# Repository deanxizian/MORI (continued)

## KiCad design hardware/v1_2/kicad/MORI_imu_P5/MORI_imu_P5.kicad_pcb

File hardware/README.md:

# 硬件

当前成品为 **成品模块 + 一块自制驱动/载板**。原自制电源、IMU、后接口板已退出设计方向。

| 部分 | 当前选择/入口 |
|---|---|
| 自制驱动/载板 | [C3 R108P](driver/README.md)，40 项未连接，不可制造 |
| 主控 | WeAct STM32F412RET6 64Pin V1.1 |
| UPS | 微雪 UPS Module 3S，原配 DC 口与总开关 |
| IMU | DFRobot BMI323 / SEN0693，使用板载小插座 |
| 头部 | 微雪 CAM33700 / OV3660、1.85inch Touch LCD Module / LCD35079 |
| 舵机 | S288 ×2、SCS0009 SC-0090-C001 ×2 |
| 音频 | CAM 板载音频 + SP3040 喇叭 |

[采购记录](../mechanical/procurement/采购记录.md)记录已买状态和当时价格；[当前板 BOM](driver/bom_candidate.csv)是尚未发布制造的开发候选；[线束表](driver/harness/README.md)未给裁切长度。

正式共享合同仍为 [IF-C1-R4](../contracts/components.json)，C3 R108P 还未晋升合同。主模型是 M1.58，旧载板/外置 Buck 尚未替换。旧多板数据收在 [机械构建参考](../mechanical/input_assets/pcb_reference/README.md)，不是当前采购列表。

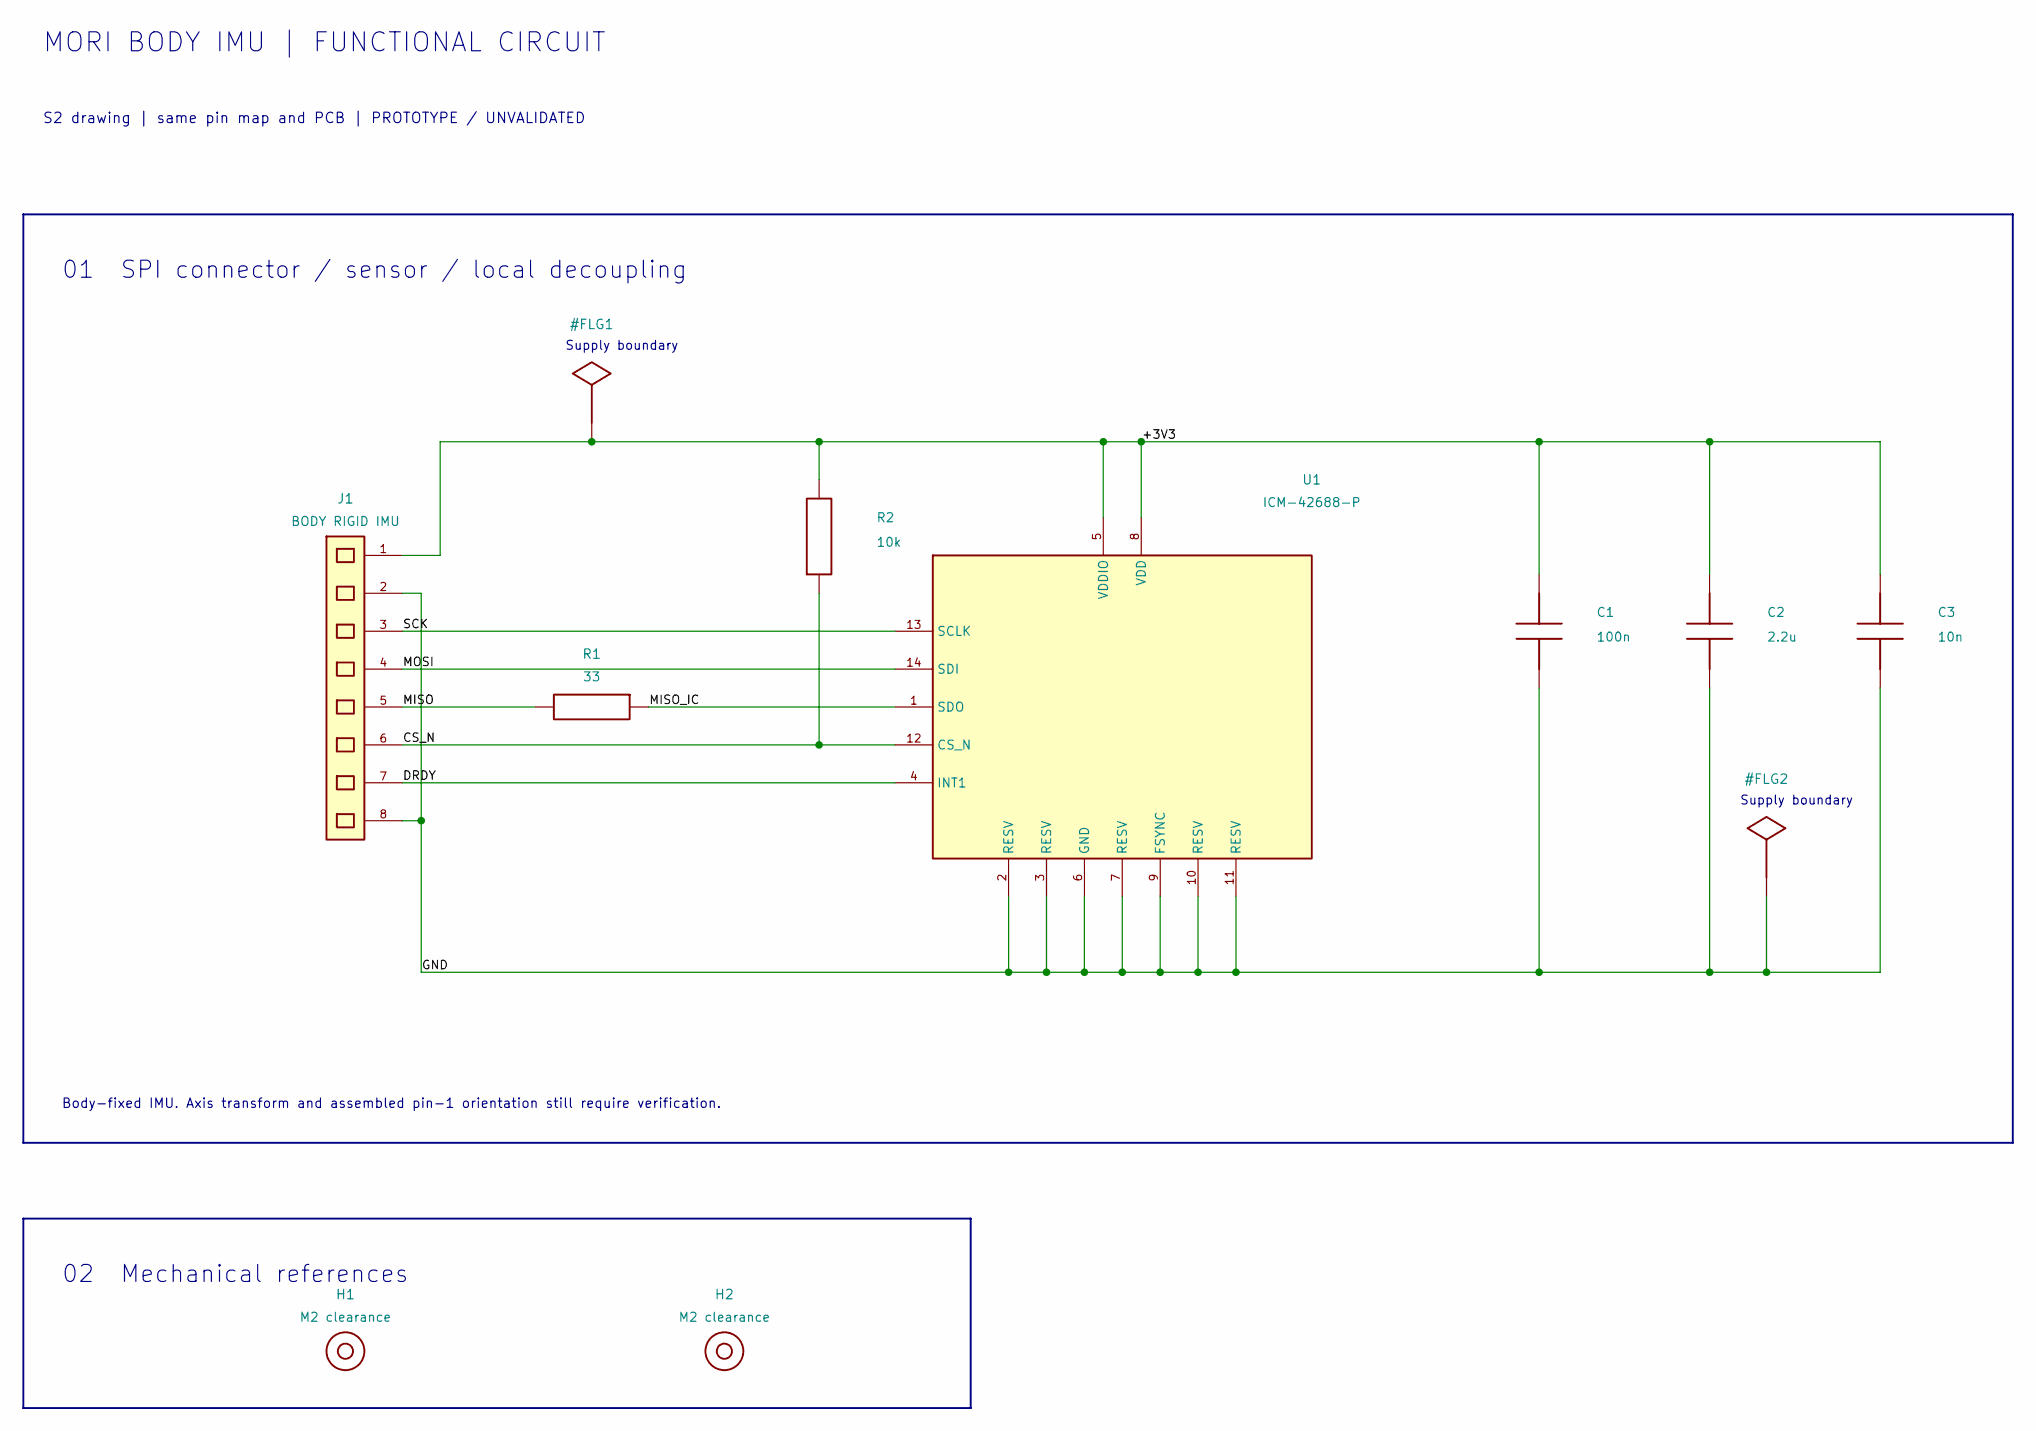
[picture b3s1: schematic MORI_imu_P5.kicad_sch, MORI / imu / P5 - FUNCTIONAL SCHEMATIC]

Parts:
C1: 100n; C_0603_1608Metric
C2: 2.2u; C_0603_1608Metric
C3: 10n; C_0603_1608Metric
H1, H2: M2 clearance; MountingHole_2.2mm_M2
J1: BODY RIGID IMU; JST_PH_B8B-PH-K_1x08_P2.00mm_Vertical__P4_PH_ANNULUS__P5_J1
R1: 33; R_0603_1608Metric
R2: 10k; R_0603_1608Metric
U1: ICM-42688-P; TDK_ICM42688P_LGA14_3x2p5__P2_U1__P3R1_U1

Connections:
/+3V3: C1.1, C2.1, C3.1, J1.1, R2.2, U1.5 (VDDIO), U1.8 (VDD)
/CS_N: J1.6, R2.1, U1.12 (CS_N)
/DRDY: J1.7, U1.4 (INT1)
/GND: C1.2, C2.2, C3.2, J1.2, J1.8, U1.2 (RESV), U1.3 (RESV), U1.6 (GND), U1.7 (RESV), U1.9 (FSYNC), U1.10 (RESV), U1.11 (RESV)
/MISO: J1.5, R1.2
/MISO_IC: R1.1, U1.1 (SDO)
/MOSI: J1.4, U1.14 (SDI)
/SCK: J1.3, U1.13 (SCLK)

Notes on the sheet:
MORI BODY IMU | FUNCTIONAL CIRCUIT
S2 drawing | same pin map and PCB | PROTOTYPE / UNVALIDATED
01 SPI connector / sensor / local decoupling
Body-fixed IMU. Axis transform and assembled pin-1 orientation still require verification.
Supply boundary
02 Mechanical references

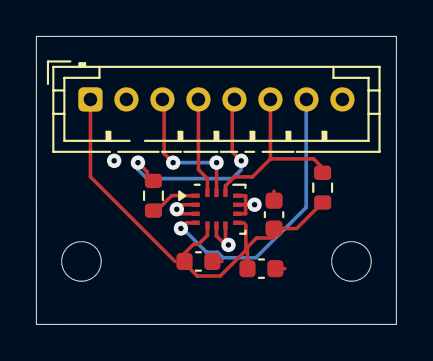
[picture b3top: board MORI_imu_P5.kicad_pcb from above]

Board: 2 copper layers, 20.0 x 16.0 mm, 9 parts (0 on the bottom side), 8 nets.

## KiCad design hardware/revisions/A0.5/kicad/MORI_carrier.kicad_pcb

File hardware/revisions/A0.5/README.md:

# MORI 硬件设计增量 A0.5

本轮已经完成保护电路补充、可复核的载板布线、固件修复和独立机械校核。**这是待实物验证的工程增量，尚未放行整机装配或PCB生产。** 原机械工程和A0.4档案保留；并行软件目录未改写。

## 已落地的内容

|内容|本轮结果|
|---|---|
|最小固件|修复ESP-IDF5.5.2的LEDC初始化遗漏；输出失败锁存并撤销ARM；实际构建通过；195项模拟断言通过|
|舵机信号|增加SN74LVC1T45的断电隔离、电源去耦和输出下拉；GPIO41与脉宽定义不变|
|原生KiCad|80个封装、1074条走线/过孔、2个GND铜区；ERC=0；DRC违规=0、未连接=0、原理图一致性问题=0|
|跨文件核对|242个引脚网络、94行载板接线；GPIO、默认运动锁定和原机械源保持一致|
|独立机械模型|主控与头部支柱的包络冲突已量化；电池托架加长；IMU真实孔位已加入|
|试打文件|电池托架54×92×7.45和IMU孔距试片30×22×2.4；闭合单实体，已重新导入校核尺寸|
|软件交接|Pololu4863 / 979.616计数每转继续作为硬件执行基线；无需等待电池与外壳定型才开始模拟/协议开发|

先看 [机械校核与试打件](mechanical/README.md)、[电路增量和布局限制](electrical_changes.md)、[软件接口决策](interface_decisions.md)、[验证记录](reports/verification.md)。采购仍按 [本版BOM](bom.csv) 的状态执行，未下单、未刷写、未生成Gerber/钻孔文件。

## 仍然卡住最终装配/制造的事项

- DevKit的71×28×18保守包络与现有框架相交约640.179mm³。主控先外置台架；低矮安装、更紧凑板或内部支柱修改需要进一步确定，不能直接缩放模型。
- 载板的部分去耦电容离IC过远，局部电源与回流还要重排；器件高度、插拔和线缆空间尚未通过装配检查。DRC通过只说明列出的电气几何规则满足。
- Ø60最终显示屏仍未确定；小GC9A01只用于台架。电池规格表有尺寸矛盾，充电电流、保护/均衡和再生路径资料未补齐。
- 同步带轮含轮毂总宽、皮带SKU、舵机安装耳/花键、25×37×7头轴承座/主轴仍需闭合。具体索取内容已写成 [采购问题清单](procurement_questions.md)。
- 所有实际上电、急停、热测试、惯量辨识、头部行程和自由平衡验证均为 **NOT_TESTED**。三个运动编译门仍为n。

## 文件入口

- `kicad/MORI_carrier.kicad_pro`：完整原生KiCad工程与本地库。
- `mechanical/MORI_Hardware_Fit_A0.5.blend`：独立装配校核副本。
- `mechanical/Battery_Tray_A05_TRIAL.stl`、`mechanical/IMU_20p32_Hole_Gauge.stl`：试打件，不是整机最终零件发布。
- `firmware/`：硬件最小验证基线；并行软件继续在根目录`software/`。
- `tools/`、`tests/`、`reports/`：生成脚本、测试及实际运行记录。
- `sources/manifest.json`：本轮厂家CAD/数据手册来源与哈希。

本目录作为A0.5增量使用。机械生成脚本读取现有MORI根目录的`params.json`、`reports/derived.json`和原Blender；不会替换这些文件。整机预算仍引用A0.4的未验证估算；新增隔离器件组预留US$1.50，试打托架相对旧托架按实心PLA估算增加0.301g，均非实测。

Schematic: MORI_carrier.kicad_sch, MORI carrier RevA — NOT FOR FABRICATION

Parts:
C1: 1uF_50V_X7R; C_0805_2012Metric
C2, C3, C4, C5, C6, C13, C14, C15: 100nF; C_0805_2012Metric
C7: 100nF_25V; C_0805_2012Metric
C8: 1nF_C0G; C_0805_2012Metric
C9: 1000uF_16V; CP_Radial_D10.0mm_P5.00mm
C10: 470uF_10V; CP_Radial_D10.0mm_P5.00mm
C11: 100uF_10V; CP_Radial_D10.0mm_P5.00mm
C12: 100uF_16V; CP_Radial_D10.0mm_P5.00mm
D1: SS34_USB_ISOLATION; D_SMA
H1, H2, H3, H4: M3_deck_hole_3.4mm; MountingHole_3.4mm_M3
J1: VMAIN_from_protected_pack; TerminalBlock_Phoenix_MKDS-1,5-2_1x02_P5.00mm_Horizontal
J2: DevKit_v1.1_N8R8_HARNESS; IDC-Header_2x13_P2.54mm_Vertical
J3: DRV8833_Pololu2130_HARNESS; JST_XH_B14B-XH-A_1x14_P2.50mm_Vertical
J4, J5: Motor4863_CUSTOM_XH6; JST_XH_B6B-XH-A_1x06_P2.50mm_Vertical
J6: Adafruit4438_IMU; JST_XH_B5B-XH-A_1x05_P2.50mm_Vertical
J7: INA219_LOGIC; JST_SH_BM04B-SRSS-TB_1x04-1MP_P1.00mm_Vertical
J8: INA219_SHUNT_IN_OUT; TerminalBlock_Phoenix_MKDS-1,5-2_1x02_P5.00mm_Horizontal
J9: Waveshare19192_LCD; JST_PH_B8B-PH-K_1x08_P2.00mm_Vertical
J10: SER0037_JR_GND_5V_SIGNAL; PinHeader_1x03_P2.54mm_Vertical
J11: ESTOP_2NC_EXTERNAL; JST_VH_B4P-VH_1x04_P3.96mm_Vertical
J12: BUCK_LOGIC_UNPLUG_FOR_USB; JST_XH_B3B-XH-A_1x03_P2.50mm_Vertical
J13: BUCK_SERVO_D24V22F5; JST_XH_B3B-XH-A_1x03_P2.50mm_Vertical
J14: DevKit_5V_KEEP_FOR_ENCODERS; JST_XH_B2B-XH-A_1x02_P2.50mm_Vertical
J15, J16: 10k_B3380_ON_MOTOR; JST_XH_B2B-XH-A_1x02_P2.50mm_Vertical
J17: DUMP_RESISTOR_HS25_5R6J; TerminalBlock_Phoenix_MKDS-1,5-2_1x02_P5.00mm_Horizontal
Q1: IRLZ44NPBF_DUMP; TO-220-3_Vertical
R1, R2, R3, R4, R5: 10k; R_0805_2012Metric
R6: 47k; R_0805_2012Metric
R7: 30k_1pct; R_0805_2012Metric
R8, R10, R11: 10k_1pct; R_0805_2012Metric
R9, R12, R13: 1k; R_0805_2012Metric
R14: 25k5_0.1pct; R_0805_2012Metric
R15: 10k_0.1pct; R_0805_2012Metric
R16: 2M2_1pct; R_0805_2012Metric
R17: 2k2; R_0805_2012Metric
R18: 4k7; R_0805_2012Metric
R19: 100R; R_0805_2012Metric
R20, R21, R22, R23, R24, R25: 100k; R_0805_2012Metric
TP1: GND; TestPoint_Pad_D1.5mm
TP2: VMAIN; TestPoint_Pad_D1.5mm
TP3: VM_MOTOR; TestPoint_Pad_D1.5mm
TP4: DEVKIT_5V; TestPoint_Pad_D1.5mm
TP5: 3V3; TestPoint_Pad_D1.5mm
TP6: ARM; TestPoint_Pad_D1.5mm
TP7: WD_OK; TestPoint_Pad_D1.5mm
TP8: NSLEEP; TestPoint_Pad_D1.5mm
TP9: NFAULT; TestPoint_Pad_D1.5mm
TP10: BUS_DIV; TestPoint_Pad_D1.5mm
TP11: CLAMP_OUT; TestPoint_Pad_D1.5mm
U1: CD74HC123E; DIP-16_W7.62mm
U2: SN74HC08N; DIP-14_W7.62mm
U3: LM393P; DIP-8_W7.62mm
U4: TL431BCLP; TO-92_Inline
U5: SN74LVC14AD; SOIC-14_3.9x8.7mm_P1.27mm
U6: SN74LVC1T45DBVR; SOT-23-6

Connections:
/3V3: C2.1, C3.1, C13.1, C14.1, J2.25 (3V3), J6.1 (3V3), J7.2 (3V3), J9.1 (3V3), J9.8 (3V3), J11.1 (3V3), R4.1, R6.1, R10.1, R11.1, TP5.1, U1.16 (VCC), U2.14 (VCC), U5.14 (VCC), U6.1 (VCCA), U6.5 (DIR)
/AIN1: J2.4 (AIN1), J3.4 (AIN1)
/AIN2: J2.5 (AIN2), J3.5 (AIN2)
/ARM: J2.18 (ARM), R1.1, TP6.1, U1.3 (1CLR), U2.1 (1A)
/ARM_WD: U2.3 (1Y), U2.4 (2A)
/BAT_ADC: C4.1, J2.1 (BAT_ADC), R9.2
/BAT_DIV: R7.2, R8.1, R9.1
/BIN1: J2.6 (BIN1), J3.6 (BIN1)
/BIN2: J2.7 (BIN2), J3.7 (BIN2)
/BUS_DIV: C8.1, R14.2, R15.1, R16.2, TP10.1, U3.3 (IN1+)
/CLAMP_OUT: R16.1, R18.2, R19.1, TP11.1, U3.1 (OUT1)
/DEVKIT_5V: D1.1 (K), J4.4 (VCC), J5.4 (VCC), J14.1 (DEVKIT_5V), TP4.1
/DUMP_DRAIN: J17.2 (DUMP_DRAIN), Q1.2 (D)
/DUMP_GATE: Q1.1 (G), R19.2, R20.1
/ENC_LA: J2.8 (ENC_LA), U5.2 (1Y)
/ENC_LA_5V: J4.3 (A), R21.1, U5.1 (1A)
/ENC_LB: J2.9 (ENC_LB), U5.4 (2Y)
/ENC_LB_5V: J4.2 (B), R22.1, U5.3 (2A)
/ENC_RA: J2.10 (ENC_RA), U5.6 (3Y)
/ENC_RA_5V: J5.3 (A), R23.1, U5.5 (3A)
/ENC_RB: J2.11 (ENC_RB), U5.8 (4Y)
/ENC_RB_5V: J5.2 (B), R24.1, U5.9 (4A)
/ESTOP_OK: J2.24 (ESTOP_OK), J11.2 (ESTOP_OK), R3.1, U2.5 (2B)
/GND: C2.2, C3.2, C4.2, C5.2, C6.2, C7.2, C8.2, C9.2 (-), C10.2 (-), C11.2 (-), C12.2 (-), C13.2, C14.2, C15.2, J1.2 (GND), J2.26 (GND), J3.3 (GND), J3.14 (GND), J4.1 (GND), J5.1 (GND), J6.2 (GND), J7.1 (GND), J9.2 (GND), J10.1 (GND), J12.2 (GND), J13.2 (GND), J14.2 (GND), J15.2 (GND), J16.2 (GND), Q1.3 (S), R1.2, R2.2, R3.2, R5.2, R8.2, R15.2, R20.2, R21.2, R22.2, R23.2, R24.2, R25.2, TP1.1, U1.1 (1A), U1.8 (GND), U1.9 (2A), U1.10 (2B), U1.11 (2CLR), U2.7 (GND), U2.12 (4A), U2.13 (4B), U3.4 (V-), U3.5 (IN2+), U4.2 (A), U5.7 (GND), U5.11 (5A), U5.13 (6A), U6.2 (GND)
/HEAD_5V: C15.1, J10.2 (HEAD_5V), J11.4 (HEAD_5V), U6.6 (VCCB)
/HEAD_PWM: J2.21 (HEAD_PWM), U6.3 (A)
/HEAD_SIGNAL_5V: J10.3 (HEAD_PWM), R25.1, U6.4 (B)
/HEARTBEAT: J2.22 (HEARTBEAT), R2.1, U1.2 (1B)
/IMU_INT: J2.15 (IMU_INT), J6.5 (IMU_INT)
/LCD_CLK: J2.13 (LCD_CLK), J9.4 (LCD_CLK)
/LCD_CS: J2.14 (LCD_CS), J9.5 (LCD_CS)
/LCD_DC: J2.19 (LCD_DC), J9.6 (LCD_DC)
/LCD_MOSI: J2.12 (LCD_MOSI), J9.3 (LCD_MOSI)
/LCD_RST: J2.20 (LCD_RST), J9.7 (LCD_RST)
/LM1: J3.10 (LM1), J4.6 (M1)
/LM2: J3.11 (LM2), J4.5 (M2)
/LOGIC_5V_RAW: C11.1 (+), D1.2 (A), J12.3 (LOGIC_5V_RAW)
/NFAULT: J2.23 (NFAULT), J3.9 (NFAULT), R4.2, TP9.1, U2.10 (3B)
/NSLEEP: J3.8 (NSLEEP), R5.1, TP8.1, U2.8 (3Y)
/NTC_L: C5.1, J2.2 (NTC_L), R12.2
/NTC_L_RAW: J15.1 (NTC_L_RAW), R10.2, R12.1
/NTC_R: C6.1, J2.3 (NTC_R), R13.2
/NTC_R_RAW: J16.1 (NTC_R_RAW), R11.2, R13.1
/RM1: J3.12 (RM1), J5.6 (M1)
/RM2: J3.13 (RM2), J5.5 (M2)
/RUN_OK: U2.6 (2Y), U2.9 (3A)
/SCL: J2.17 (SCL), J6.4 (SCL), J7.4 (SCL)
/SDA: J2.16 (SDA), J6.3 (SDA), J7.3 (SDA)
/SERVO_5V_RAW: C10.1 (+), J11.3 (SERVO_5V_RAW), J13.3 (SERVO_5V_RAW)
/VMAIN: C12.1 (+), J1.1 (VMAIN), J8.1 (VMAIN), J12.1 (VMAIN), J13.1 (VMAIN), R7.1, TP2.1
/VM_DRV_IN: J3.1 (VM_DRV_IN), J8.2 (VM_DRV_IN)
/VM_MOTOR: C7.1, C9.1 (+), J3.2 (VM_MOTOR), J17.1 (VM_MOTOR), R14.1, R17.1, R18.1, TP3.1, U3.8 (V+)
/VREF_2V495: R17.2, U3.2 (IN1-), U3.6 (IN2-), U4.1 (REF), U4.3 (K)
/WD_C: C1.1, U1.14 (1C)
/WD_OK: TP7.1, U1.13 (1Q), U2.2 (1B)
/WD_RC: C1.2, R6.2, U1.15 (1RC)

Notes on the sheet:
MORI RevA — PROTOTYPE / UNVALIDATED — module harness + safety circuitry; see wiring.csv for offboard paths

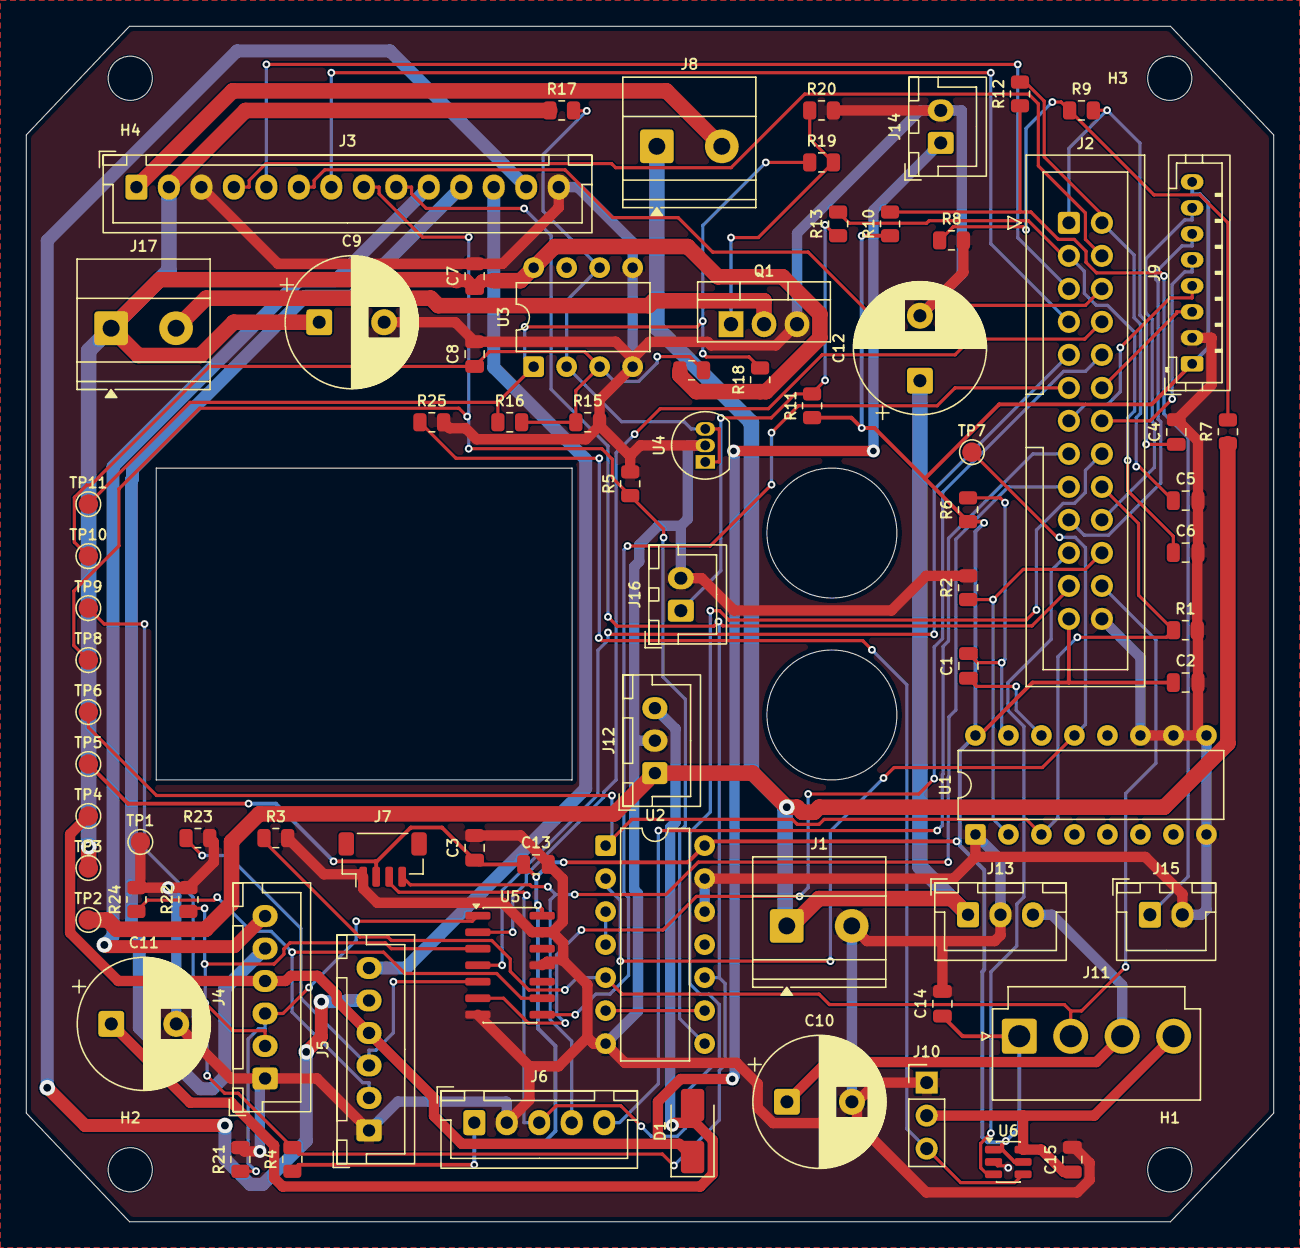
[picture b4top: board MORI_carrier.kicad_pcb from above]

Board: 2 copper layers, 96.0 x 92.0 mm, 80 parts (0 on the bottom side), 56 nets.

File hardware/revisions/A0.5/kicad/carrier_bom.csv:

ref,value,footprint,section,note
J1,VMAIN_from_protected_pack,"TerminalBlock_Phoenix:TerminalBlock_Phoenix_MKDS-1,5-2_1x02_P5.00mm_Horizontal",POWER,
J2,DevKit_v1.1_N8R8_HARNESS,Connector_IDC:IDC-Header_2x13_P2.54mm_Vertical,IO,Remote board represented with functional pin directions
J3,DRV8833_Pololu2130_HARNESS,Connector_JST:JST_XH_B14B-XH-A_1x14_P2.50mm_Vertical,IO,
J4,Motor4863_CUSTOM_XH6,Connector_JST:JST_XH_B6B-XH-A_1x06_P2.50mm_Vertical,IO,CUSTOM retermination:1 green GND;2 white B;3 yellow A;4 blue Vcc 5V;5 black M2;6 red M1. NOT factory header order. LVC14 level shifts required.
J5,Motor4863_CUSTOM_XH6,Connector_JST:JST_XH_B6B-XH-A_1x06_P2.50mm_Vertical,IO,CUSTOM retermination:1 green GND;2 white B;3 yellow A;4 blue Vcc 5V;5 black M2;6 red M1. NOT factory header order. LVC14 level shifts required.
J6,Adafruit4438_IMU,Connector_JST:JST_XH_B5B-XH-A_1x05_P2.50mm_Vertical,IO,
J7,INA219_LOGIC,Connector_JST:JST_SH_BM04B-SRSS-TB_1x04-1MP_P1.00mm_Vertical,IO,
J8,INA219_SHUNT_IN_OUT,"TerminalBlock_Phoenix:TerminalBlock_Phoenix_MKDS-1,5-2_1x02_P5.00mm_Horizontal",POWER,
J9,Waveshare19192_LCD,Connector_JST:JST_PH_B8B-PH-K_1x08_P2.00mm_Vertical,IO,
J10,SER0037_JR_GND_5V_SIGNAL,Connector_PinHeader_2.54mm:PinHeader_1x03_P2.54mm_Vertical,IO,A0.5: PWM via SN74LVC1T45; HEAD_5V from switched NC2. Both rails power-off behavior must be tested.
J11,ESTOP_2NC_EXTERNAL,Connector_JST:JST_VH_B4P-VH_1x04_P3.96mm_Vertical,SAFETY,
J12,BUCK_LOGIC_UNPLUG_FOR_USB,Connector_JST:JST_XH_B3B-XH-A_1x03_P2.50mm_Vertical,POWER,UNPLUG whole J12 logic-buck harness before USB; manufacturer power modes mutually exclusive. Keep J14 connected so USB also supplies encoder 5V. Battery may power motors/head separately.
J13,BUCK_SERVO_D24V22F5,Connector_JST:JST_XH_B3B-XH-A_1x03_P2.50mm_Vertical,POWER,
J14,DevKit_5V_KEEP_FOR_ENCODERS,Connector_JST:JST_XH_B2B-XH-A_1x02_P2.50mm_Vertical,POWER,KEEP J14 connected in both supply modes: DevKit 5V and encoder bus. Disconnect J12 logic buck before USB; do not cut encoder power by unplugging J14.
J15,10k_B3380_ON_MOTOR,Connector_JST:JST_XH_B2B-XH-A_1x02_P2.50mm_Vertical,IO,
J16,10k_B3380_ON_MOTOR,Connector_JST:JST_XH_B2B-XH-A_1x02_P2.50mm_Vertical,IO,
J17,DUMP_RESISTOR_HS25_5R6J,"TerminalBlock_Phoenix:TerminalBlock_Phoenix_MKDS-1,5-2_1x02_P5.00mm_Horizontal",CLAMP,
U1,CD74HC123E,Package_DIP:DIP-16_W7.62mm,SAFETY,
U2,SN74HC08N,Package_DIP:DIP-14_W7.62mm,SAFETY,
U5,SN74LVC14AD,Package_SO:SOIC-14_3.9x8.7mm_P1.27mm,ENCODER,
C13,100nF,Capacitor_SMD:C_0805_2012Metric,ENCODER,
U3,LM393P,Package_DIP:DIP-8_W7.62mm,CLAMP,
U4,TL431BCLP,Package_TO_SOT_THT:TO-92_Inline,CLAMP,
Q1,IRLZ44NPBF_DUMP,Package_TO_SOT_THT:TO-220-3_Vertical,CLAMP,
D1,SS34_USB_ISOLATION,Diode_SMD:D_SMA,POWER,
R1,10k,Resistor_SMD:R_0805_2012Metric,SAFETY,
R2,10k,Resistor_SMD:R_0805_2012Metric,SAFETY,
R3,10k,Resistor_SMD:R_0805_2012Metric,SAFETY,
R4,10k,Resistor_SMD:R_0805_2012Metric,SAFETY,
R5,10k,Resistor_SMD:R_0805_2012Metric,SAFETY,
R6,47k,Resistor_SMD:R_0805_2012Metric,SAFETY,
R7,30k_1pct,Resistor_SMD:R_0805_2012Metric,ADC,
R8,10k_1pct,Resistor_SMD:R_0805_2012Metric,ADC,
R9,1k,Resistor_SMD:R_0805_2012Metric,ADC,
R10,10k_1pct,Resistor_SMD:R_0805_2012Metric,ADC,
R11,10k_1pct,Resistor_SMD:R_0805_2012Metric,ADC,
R12,1k,Resistor_SMD:R_0805_2012Metric,ADC,
R13,1k,Resistor_SMD:R_0805_2012Metric,ADC,
R14,25k5_0.1pct,Resistor_SMD:R_0805_2012Metric,CLAMP,
R15,10k_0.1pct,Resistor_SMD:R_0805_2012Metric,CLAMP,
R16,2M2_1pct,Resistor_SMD:R_0805_2012Metric,CLAMP,
R17,2k2,Resistor_SMD:R_0805_2012Metric,CLAMP,
R18,4k7,Resistor_SMD:R_0805_2012Metric,CLAMP,
R19,100R,Resistor_SMD:R_0805_2012Metric,CLAMP,
R20,100k,Resistor_SMD:R_0805_2012Metric,CLAMP,
R21,100k,Resistor_SMD:R_0805_2012Metric,ENCODER,
R22,100k,Resistor_SMD:R_0805_2012Metric,ENCODER,
R23,100k,Resistor_SMD:R_0805_2012Metric,ENCODER,
R24,100k,Resistor_SMD:R_0805_2012Metric,ENCODER,
C1,1uF_50V_X7R,Capacitor_SMD:C_0805_2012Metric,DECOUPLING,
C2,100nF,Capacitor_SMD:C_0805_2012Metric,DECOUPLING,
C3,100nF,Capacitor_SMD:C_0805_2012Metric,DECOUPLING,
C4,100nF,Capacitor_SMD:C_0805_2012Metric,DECOUPLING,
C5,100nF,Capacitor_SMD:C_0805_2012Metric,DECOUPLING,
C6,100nF,Capacitor_SMD:C_0805_2012Metric,DECOUPLING,
C7,100nF_25V,Capacitor_SMD:C_0805_2012Metric,DECOUPLING,
C8,1nF_C0G,Capacitor_SMD:C_0805_2012Metric,DECOUPLING,
C9,1000uF_16V,Capacitor_THT:CP_Radial_D10.0mm_P5.00mm,POWER,
C10,470uF_10V,Capacitor_THT:CP_Radial_D10.0mm_P5.00mm,POWER,
C11,100uF_10V,Capacitor_THT:CP_Radial_D10.0mm_P5.00mm,POWER,
C12,100uF_16V,Capacitor_THT:CP_Radial_D10.0mm_P5.00mm,POWER,
TP1,GND,TestPoint:TestPoint_Pad_D1.5mm,TESTPOINT,
TP2,VMAIN,TestPoint:TestPoint_Pad_D1.5mm,TESTPOINT,
TP3,VM_MOTOR,TestPoint:TestPoint_Pad_D1.5mm,TESTPOINT,
TP4,DEVKIT_5V,TestPoint:TestPoint_Pad_D1.5mm,TESTPOINT,
TP5,3V3,TestPoint:TestPoint_Pad_D1.5mm,TESTPOINT,
TP6,ARM,TestPoint:TestPoint_Pad_D1.5mm,TESTPOINT,
TP7,WD_OK,TestPoint:TestPoint_Pad_D1.5mm,TESTPOINT,
TP8,NSLEEP,TestPoint:TestPoint_Pad_D1.5mm,TESTPOINT,
TP9,NFAULT,TestPoint:TestPoint_Pad_D1.5mm,TESTPOINT,
TP10,BUS_DIV,TestPoint:TestPoint_Pad_D1.5mm,TESTPOINT,
TP11,CLAMP_OUT,TestPoint:TestPoint_Pad_D1.5mm,TESTPOINT,
U6,SN74LVC1T45DBVR,Package_TO_SOT_SMD:SOT-23-6,HEAD_ISOLATION,PROTOTYPE / UNVALIDATED
R25,100k,Resistor_SMD:R_0805_2012Metric,HEAD_ISOLATION,PROTOTYPE / UNVALIDATED
C14,100nF,Capacitor_SMD:C_0805_2012Metric,HEAD_ISOLATION,PROTOTYPE / UNVALIDATED
C15,100nF,Capacitor_SMD:C_0805_2012Metric,HEAD_ISOLATION,PROTOTYPE / UNVALIDATED
H1,M3_deck_hole_3.4mm,MORI_Mech:MountingHole_3.4mm_M3,MECHANICAL,"copied deck XY, standoff Z pending"
H2,M3_deck_hole_3.4mm,MORI_Mech:MountingHole_3.4mm_M3,MECHANICAL,"copied deck XY, standoff Z pending"
H3,M3_deck_hole_3.4mm,MORI_Mech:MountingHole_3.4mm_M3,MECHANICAL,"copied deck XY, standoff Z pending"
H4,M3_deck_hole_3.4mm,MORI_Mech:MountingHole_3.4mm_M3,MECHANICAL,"copied deck XY, standoff Z pending"
